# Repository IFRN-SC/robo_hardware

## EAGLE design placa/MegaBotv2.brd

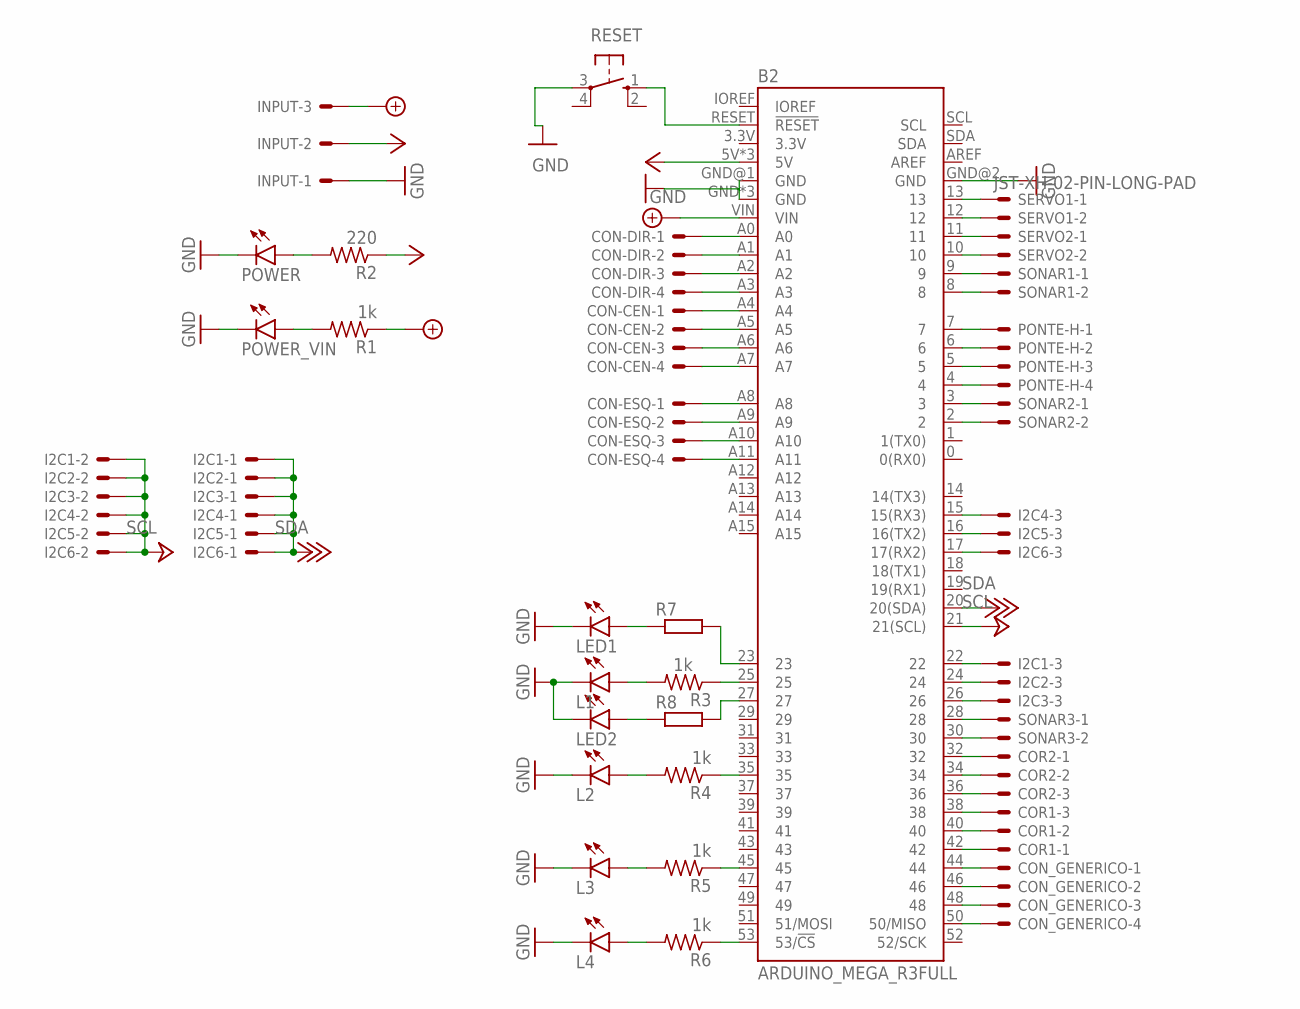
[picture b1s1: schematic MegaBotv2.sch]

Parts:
B2: ARDUINO_MEGA_R3FULL; ARDUINO_MEGA_NO_SILK
CON-CEN: JST-XH-04-PIN-LONG-PAD; JST-XH-04-PACKAGE-LONG-PAD
CON-DIR: JST-XH-04-PIN-LONG-PAD; JST-XH-04-PACKAGE-LONG-PAD
CON-ESQ: JST-XH-04-PIN-LONG-PAD; JST-XH-04-PACKAGE-LONG-PAD
CON_GENERICO: JST-XH-04-PIN-LONG-PAD; JST-XH-04-PACKAGE-LONG-PAD
COR1, COR2: JST-XH-03-PIN-LONG-PAD; JST-XH-03-PACKAGE-LONG-PAD
I2C1, I2C2, I2C3, I2C4, I2C5, I2C6: JST-XH-03-PIN-LONG-PAD; JST-XH-03-PACKAGE-LONG-PAD
INPUT: KK-156-3
L1, L2, L3, L4: LEDLED5MM_LONG_PAD; LED5MM_LONG_PAD
LED1, LED2: LEDKA-3528ASYC; KA-3528ASYC
PONTE-H: JST-XH-04-PIN-LONG-PAD; JST-XH-04-PACKAGE-LONG-PAD
POWER: LEDLED5MM_LONG_PAD; LED5MM_LONG_PAD
POWER_VIN: LEDLED5MM_LONG_PAD; LED5MM_LONG_PAD
R1, R3, R4, R5, R6: 1k; 0204/7
R2: 220; 0204/7
R7, R8: R-EU_M0805; M0805
RESET: 10-XX; B3F-10XX
SERVO1, SERVO2: JST-XH-02-PIN-LONG-PAD; JST-XH-02-PACKAGE-LONG-PAD
SONAR1, SONAR2, SONAR3: JST-XH-02-PIN-LONG-PAD; JST-XH-02-PACKAGE-LONG-PAD

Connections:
+8V: B2.VIN, INPUT.3, R1.1
+18V: B2.20 (20(SDA)), I2C1.1, I2C2.1, I2C3.1, I2C4.1, I2C5.1, I2C6.1
+24V: B2.21 (21(SCL)), I2C1.2, I2C2.2, I2C3.2, I2C4.2, I2C5.2, I2C6.2
GND: B2.GND, B2.GND@1 (GND), B2.GND@2 (GND), B2.GND@3 (GND), B2.GND@4 (GND), INPUT.1, L1.K (C), L2.K (C), L3.K (C), L4.K (C), LED1.C, LED2.C, POWER.K (C), POWER_VIN.K (C), RESET.3
unnamed: B2.7, PONTE-H.1
unnamed: B2.6, PONTE-H.2
unnamed: B2.5, PONTE-H.3
unnamed: B2.4, PONTE-H.4
unnamed: B2.A1, CON-DIR.2
unnamed: B2.A2, CON-DIR.3
unnamed: B2.A3, CON-DIR.4
unnamed: B2.A4, CON-CEN.1
unnamed: B2.A5, CON-CEN.2
unnamed: B2.A6, CON-CEN.3
unnamed: B2.A0, CON-DIR.1
unnamed: B2.A7, CON-CEN.4
unnamed: B2.A8, CON-ESQ.1
unnamed: B2.A9, CON-ESQ.2
unnamed: B2.A10, CON-ESQ.3
unnamed: B2.A11, CON-ESQ.4
unnamed: B2.11, SERVO2.1
unnamed: B2.10, SERVO2.2
unnamed: B2.9, SONAR1.1
unnamed: B2.8, SONAR1.2
unnamed: B2.22, I2C1.3
unnamed: B2.24, I2C2.3
unnamed: B2.26, I2C3.3
unnamed: B2.15 (15(RX3)), I2C4.3
unnamed: B2.16 (16(TX2)), I2C5.3
unnamed: B2.17 (17(RX2)), I2C6.3
unnamed: B2.13, SERVO1.1
unnamed: B2.12, SERVO1.2
unnamed: POWER_VIN.A, R1.2
unnamed: B2.32, COR2.1
unnamed: B2.34, COR2.2
unnamed: POWER.A, R2.2
unnamed: B2.36, COR2.3
unnamed: B2.38, COR1.3
unnamed: B2.40, COR1.2
unnamed: B2.42, COR1.1
unnamed: L1.A, R3.2
unnamed: L2.A, R4.2
unnamed: L3.A, R5.2
unnamed: L4.A, R6.2
unnamed: B2.25, R3.1
unnamed: B2.35, R4.1
unnamed: B2.45, R5.1
unnamed: B2.53 (53/!CS), R6.1
unnamed: B2.RESET (!RESET), RESET.1 (S)
unnamed: B2.3, SONAR2.1
unnamed: B2.2, SONAR2.2
unnamed: B2.28, SONAR3.1
unnamed: B2.30, SONAR3.2
unnamed: B2.44, CON_GENERICO.1
unnamed: B2.46, CON_GENERICO.2
unnamed: B2.48, CON_GENERICO.3
unnamed: B2.50 (50/MISO), CON_GENERICO.4
unnamed: LED1.A, R7.1
unnamed: B2.23, R7.2
unnamed: B2.27, R8.2
unnamed: LED2.A, R8.1
VCC: B2.5V, B2.5V@1 (5V), B2.5V@2 (5V), INPUT.2, R2.1

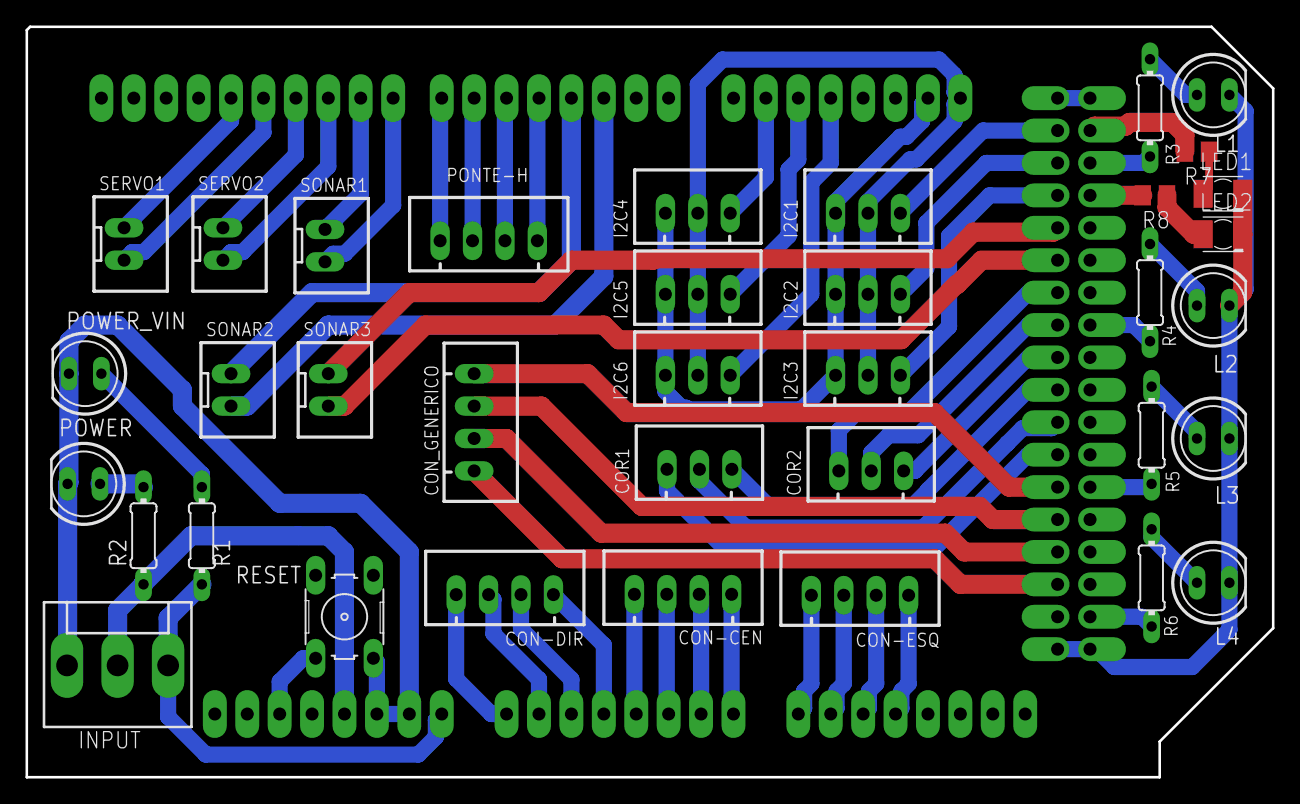
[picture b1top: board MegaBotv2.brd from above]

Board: 2 copper layers, 97.7 x 58.8 mm, 37 parts (0 on the bottom side), 62 nets.

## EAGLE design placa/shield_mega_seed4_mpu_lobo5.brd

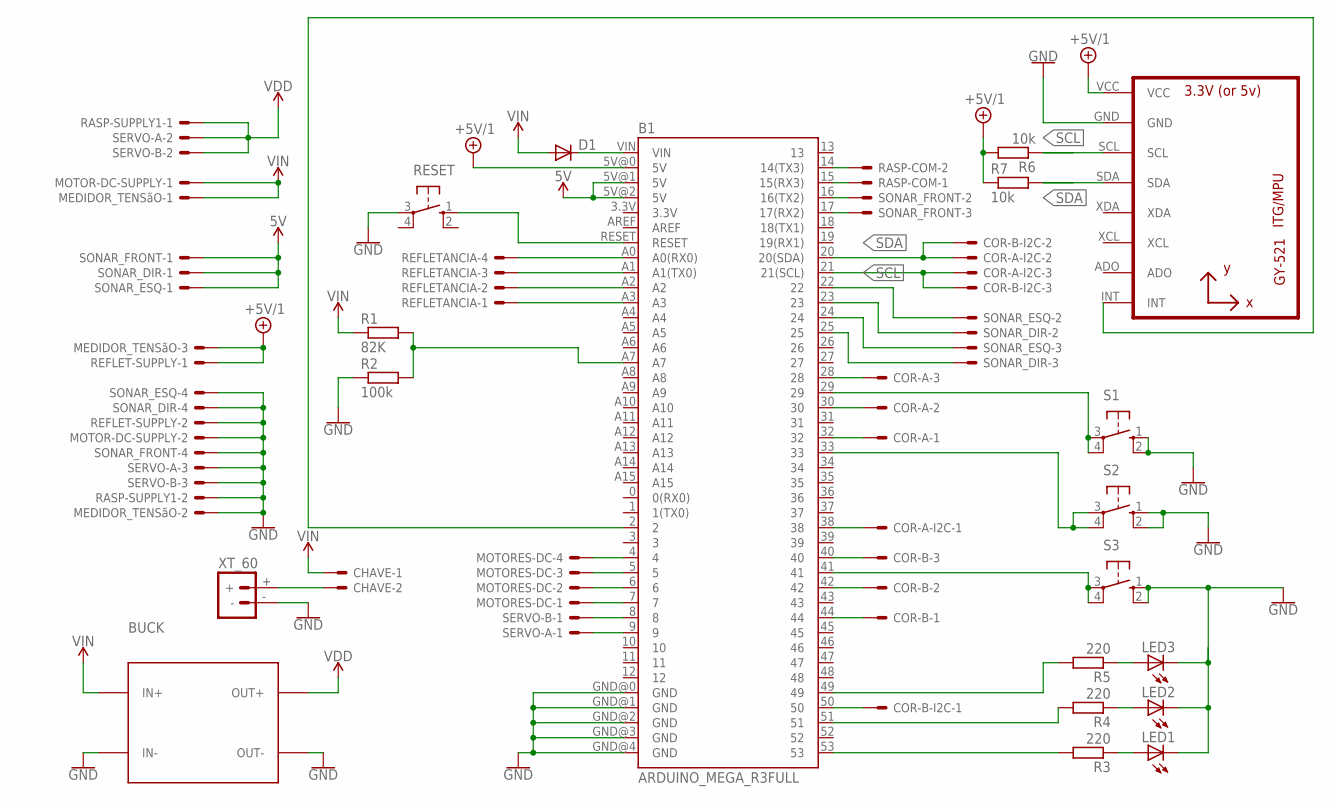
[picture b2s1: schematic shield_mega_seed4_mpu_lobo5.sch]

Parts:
B1: ARDUINO_MEGA_R3FULL; ARDUINO_MEGA
BUCK: DC-DC-STEP-DOWN-LM2596
CHAVE: 22-23-2021
COR-A: 22-23-2031
COR-A-I2C: 22-23-2031
COR-B: 22-23-2031
COR-B-I2C: 22-23-2031
D1: 1N4004; DO41-10
LED1, LED2, LED3: LED5MM
MEDIDOR_TENSãO: 22-23-2031
MOTOR-DC-SUPPLY: 22-23-2021
MOTORES-DC: 22-23-2041
R1: 82K; 0207/12
R2: 100k; 0207/12
R3, R4, R5: 220; 0207/7
R6, R7: 10k; 0204/7
RASP-COM: 22-23-2021
RASP-SUPPLY1: 22-23-2021
REFLET-SUPPLY: 22-23-2021
REFLETANCIA: 22-23-2041
RESET: 10-XX; B3F-10XX
S1, S2, S3: 10-XX; B3F-10XX
SERVO-A: 22-23-2031
SERVO-B: 22-23-2031
SONAR_DIR: 22-23-2041
SONAR_ESQ: 22-23-2041
SONAR_FRONT: 22-23-2041
U1: GY-521MPU6050; GY-521
XT_60: BATTERY_CONNXT60; XT60

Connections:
5V: B1.5V@1 (5V), B1.5V@2 (5V), SONAR_DIR.1, SONAR_ESQ.1, SONAR_FRONT.1
+5V/1: B1.5V@0 (5V), MEDIDOR_TENSãO.3, R6.2, R7.1, REFLET-SUPPLY.1, U1.VCC
GND: B1.GND@0 (GND), B1.GND@1 (GND), B1.GND@2 (GND), B1.GND@3 (GND), B1.GND@4 (GND), BUCK.IN-, BUCK.OUT-, LED1.K (C), LED2.K (C), LED3.K (C), MEDIDOR_TENSãO.2, MOTOR-DC-SUPPLY.2, R2.1, RASP-SUPPLY1.2, REFLET-SUPPLY.2, RESET.3, S1.1 (S), S1.2 (S1), S2.1 (S), S2.2 (S1), S3.1 (S), S3.2 (S1), SERVO-A.3, SERVO-B.3, SONAR_DIR.4, SONAR_ESQ.4, SONAR_FRONT.4, U1.GND, XT_60.-
unnamed: B1.A2, REFLETANCIA.2
unnamed: B1.A3, REFLETANCIA.1
unnamed: B1.4, MOTORES-DC.4
unnamed: B1.5, MOTORES-DC.3
unnamed: B1.6, MOTORES-DC.2
unnamed: B1.7, MOTORES-DC.1
unnamed: B1.8, SERVO-B.1
unnamed: B1.9, SERVO-A.1
unnamed: B1.14 (14(TX3)), RASP-COM.2
unnamed: B1.15 (15(RX3)), RASP-COM.1
unnamed: B1.16 (16(TX2)), SONAR_FRONT.2
unnamed: B1.17 (17(RX2)), SONAR_FRONT.3
unnamed: CHAVE.2, XT_60.+
unnamed: B1.32, COR-A.1
unnamed: B1.30, COR-A.2
unnamed: B1.38, COR-A-I2C.1
unnamed: B1.40, COR-B.3
unnamed: B1.42, COR-B.2
unnamed: B1.44, COR-B.1
unnamed: B1.A7, R1.2, R2.2
unnamed: B1.53, R3.2
unnamed: B1.51, R4.2
unnamed: B1.49, R5.2
unnamed: LED3.A, R5.1
unnamed: LED2.A, R4.1
unnamed: LED1.A, R3.1
unnamed: B1.33, S2.3, S2.4 (P1)
unnamed: B1.29, S1.3, S1.4 (P1)
unnamed: B1.A1 (A1(TX0)), REFLETANCIA.3
unnamed: B1.41, S3.3, S3.4 (P1)
unnamed: B1.RESET, RESET.1 (S)
unnamed: B1.VIN, D1.C
unnamed: B1.A0 (A0(RX0)), REFLETANCIA.4
unnamed: B1.25, SONAR_DIR.3
unnamed: B1.24, SONAR_ESQ.3
unnamed: B1.23, SONAR_DIR.2
unnamed: B1.22, SONAR_ESQ.2
unnamed: B1.2, U1.INT
unnamed: B1.50, COR-B-I2C.1
unnamed: B1.28, COR-A.3
SCL: B1.21 (21(SCL)), COR-A-I2C.3, COR-B-I2C.3, R6.1, U1.SCL
SDA: B1.20 (20(SDA)), COR-A-I2C.2, COR-B-I2C.2, R7.2, U1.SDA
VDD: BUCK.OUT+, RASP-SUPPLY1.1, SERVO-A.2, SERVO-B.2
VIN: BUCK.IN+, CHAVE.1, D1.A, MEDIDOR_TENSãO.1, MOTOR-DC-SUPPLY.1, R1.1

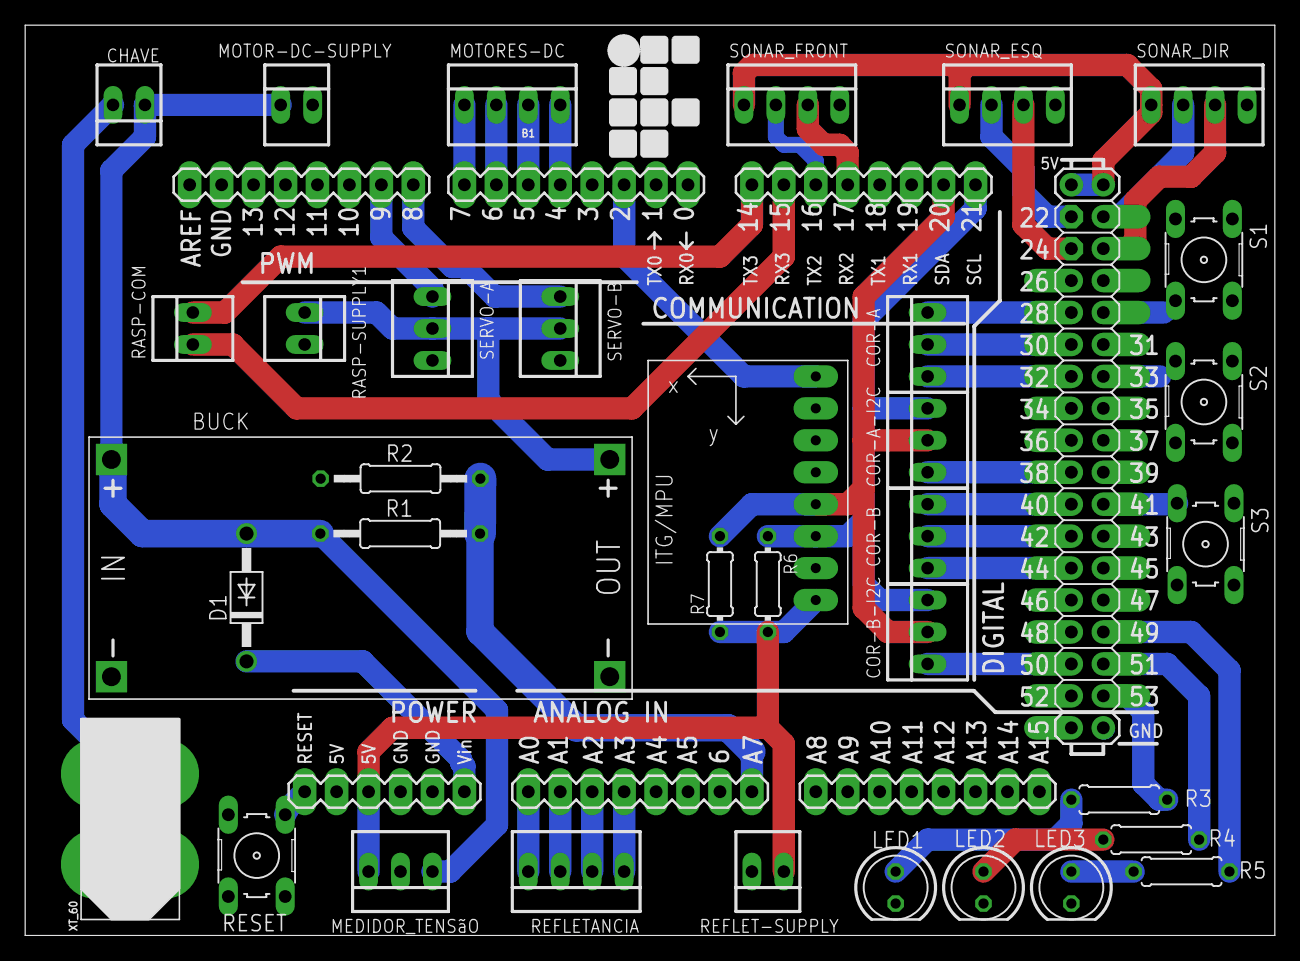
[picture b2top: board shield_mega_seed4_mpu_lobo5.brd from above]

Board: 2 copper layers, 99.4 x 72.4 mm, 36 parts (0 on the bottom side), 47 nets.

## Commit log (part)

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2017-07-06 Criada a biblioteca robo_hardware
2017-07-11 Modificado o codigo para que o sensor de linha retorne valores maiores para o branco valores menores para o preto
2017-07-11 Mudanca de nome do exemplo LerSensor.ino para LerSensorRefletancia.ino
2017-07-11 removido bug: em troca de atribuicao de valores nas variaveis valor_sensor_esq e valor_sensor_dir
2017-07-11 Modificados os pinos dos sensores de cor. Os valores anteriores dos pinos estavam gerando incompatibilidade com os pinos analógicos do arduino UNO.
2017-07-11 bug removido: erro de digitação na função de robo_hadware lerSensorLinhaEsq. Esse erro provocava um sinal negativo na função.
2017-07-11 Simplificação do progrma de acionamento dos motores, além da colocação de alguns comentários
2017-07-12 Adicionado o exemplo SonarDistancia para servir de exemplo para o que for feito com o sonsar. O erro de medição aparenta estar maior do que o esperado. Verificar!
2017-07-18 Mudança nos código de pinagem levam a alterações nos comentários existentes nos exemplos. O que foi alterado foram os exemplos que usam as funcionalidades de acionar motor e ler o sonar.
2017-07-21 Adicionadas linhas de código que permitem calibrar os sonares quando o robô é configurado. Também foi adicionada um define no .h chamado CALIBRACAO_SONAR, quanto maior o valor desse define menor será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
2017-07-21 Remoção de linhas comentadas que não eram mais utilizadas
2017-07-25 Criação de dois exemplos para ler os valores dos sensor de cor. Seja no formato HSV, seja no formato RGB.
2017-08-08 Criação de exemplos de uso: como escrever dados de calibração na EEPROM e como ler dados de calibração na EEPROM.
2017-08-09 Modificação dos nomes dos arquivos robo_hardware .cpp e .h para robo_hardware2 .cpp e .h
2017-08-18 remoção de bug relacionado ao endereço BOTAO
2017-08-21 Adicionado exemplo para testes do controle PID
2017-08-21 Declaração de pinos do arduino que serão utilizados pelo encoder.
2017-08-21 Modificação para não confundir com os pinos do arduino mega
2017-08-21 adcionada a classe contr_motor. Junto a essa classe foram adicionados dois objetos do mesmo tipo.
2017-08-21 Adicionadas os arquivos para fazer controle PID
2017-08-22 acrescentado trecho de código onde o valor do setpoint para o controle de velocidade do motor esquerdo e direito são definidos
2017-08-23 Acrescentado o valor dos motores na struct DadosLog. Criada a função printDados para mandar pela serial informações conforme o gnuplot utiliza para imprimir, a função ainda não finalizada.
2017-08-26 Modificação nome das variáveis motorEsq e motorDir para contrVeloEsq e contrVeloDir em trechos de código que ainda não haviam sido modificados antes. Modificação do mesmo trecho de código em decorrên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
2017-08-26 Modificada a constante NUM_MAX_PULSOS_POR_ROTACAO para o valor de 341.2 Acrescentada a configuração dos pinos de interrupção e direção do encoder. Ambos os pinos foram configurados como entrada (INPU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
2017-08-26 Criado exemplo para testar o controle de posicao.
2017-08-27 Mudança da constante NUM_MAX_PULSOS_POR_ROTACAO.
2017-08-27 Criação do construtor por cópia da classe encoder.
2017-08-27 Adição da classe motor ao robo_hardware. Criação de objeto motorEsq.
2017-08-27 Criação da função calculaPulso para uso do encoder. Uso da variável encoder_habilitado para só fazer uso do encoder se o mesmo tenha sido inicializado no construtor.
2017-08-27 Remoção de variáveis não mais utilizadas
2017-08-27 Utilização do macro ATOMIC_BLOCK para que as variáveis modificadas em interrupções só possam ser modificadas por uma única thread. Em outras palavras a interrupção é desabilitada dentro desse macro.
    Remoção da função CalculaAnguloRelativo e getAnguloRelativo devido a inúmeros problemas que ocorreram no uso dessa função.
    Mudança de nome de variável para ficar de acordo com o padrão. Inicialização da mesma variável de forma explicita nos construtores.
2017-08-27 Criação de função estática para o loop de controle. Essa função será chamada cada vez que ocorrer uma interrupção do timer2 o qual será configurado de acordo com o tempo amostragem do controlador dos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
2017-08-27 Acrescentado a classe MSTimer2 para utilizar a interrupção do timer2 para chamar o laço de controle.
2017-08-27 inicialização do tempo de amostragem do loop de controle de acordo com o valor tempo de amostragem armazenado na classe motor_contr.
2017-08-28 Colocando o controle de posicao dentro do laço de controle. Transformada a variavel ENCODER_HABILITADO em uma constante pois a mesma só é alterada no construtor. Criada as funções para habilitar e de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
2017-08-28 Foi acrescentada variáveis compartilhadas na classe encoder. Removido o uso do macro ATOMIC_BLOCK de dentro da classe encoder.
2017-08-28 criada função do loop de controle. Sendo chamada dentro da função as respectivas funções de controle de cada motor.
2017-08-28 Adicionada a função para escrever, na porta serial, os dados que estão gravados na EEPROM do arduino. Removido da classe robo_hardware2 e colocado na classe Log as funções que permitem gravar dados n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
2017-08-28 remoção do separador no momento de imprimir os dados pela porta serial
2017-08-28 Criação de exemplo que segue linha e grava dados na memória eeprom do arduino. Os dados gravados são valores dos sensores de refletância, valores aplicados nos motores e o tempo que foi realizada a l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
2017-08-28 colocação de linha que faltava para imprimir dados
2017-11-17 Adição da classe SD para permitir gravar em um cartão de memória SD. Implementação da função write para gravar dados no cartão de memória.
2017-11-17 colocado um retorno na função configurar da classe log. Esse retorno é para indicar que a classe log foi iniciada corretamente.
    Foi criado na struct DadosLog a função salvar tempo que se encarrega de criar uma função iniciar as variáveis "microsegundos" e "segundos". Ambas a variáveis foram transformadas em privadas.
2017-11-17 Modificado o exemplo seguirLinhaLog para se adaptar as mudanças realizadas na classe Log.
2018-04-12 Criação da Classe CorHardware que conterá a abstração para todos os hardwares para detecção de cor. Modificação do local onde as estruturas RGB e HSV estão declaradas. Tranferido do arquivo Cor.h par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
2018-04-12 Modificação da classe CorHardware com funções virtuais e com funções que devem ser immplementadas dentro da própria classe.
2018-04-12 Implementação inicial da capacidade de ligar e desligar os sensores de cor específicos dessa classe.
2018-04-12 Criado a função config para configurar as portas do arduino.
2018-04-12 Tornou a classe virtual pura
2018-04-12 Criada a classe SensoresCor
2018-04-13 Instanciados os objetos da classe CorTcs23
2018-04-14 Mudanção dos sensores para ficarem na mesma linha.
2018-04-14 Modificação do cálculo do sensor de linha para diminuir a cópia de código.
2018-04-14 Modificação do exemplo para utilizar as novas funções criadas
2018-04-14 Adição das últimas funções criadas no arquivo keywords.txt
2018-04-15 Acrescentado os sensores sonares direito e esquerdo. Deletado o sensor sonar lateral.
2018-04-15 Modificação dos comentários para ter os pinos dos arduinos uno e mega
2018-04-15 Criação da funcionalidade do botão.
2018-04-16 modificação dos arquivos botao.h e led.h para a pasta led_botoes
2018-04-16 Adição das funções de leitura dos botões ao robo_hardware
2018-04-16 Modificação para permitir que os leds pisquem duas vezes
2018-04-22 Criação de Enum e variável para diferenciar os dois tipos de sensores de cor: TCS34 e TCS23. Criada função para habilitar o funcionamento de cada tipo de sensor de cor. Comentado o trecho de código p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
2018-04-22 Adição da leitura dos sensores de cor TCS34725
2018-04-24 Declaração, e criação de funções para o sonar lateral direito
2018-04-24 alteração das portas dos sensores
2018-04-25 Mudança de pinagem dos sensores de refletância.
2018-04-30 Adicionados arquivos para o funcionamento do sensor
2018-05-06 remoção de bug relacionado ao endereço BOTAO (reverted from commit e8fe684fa55554fce2d019ace361826cfb9ed8f3)
2018-05-07 Correção dos pinos - LerSensorDistancia.ino
2018-05-16 Staged - Ignore
2018-05-24 Mudança na pinagem dos sensores de refletância
2018-06-12 Pinagem correta
2018-06-15 Pinagem dos motores e rrefletância mudada.
2018-07-03 Adição de arquivos com nomes novos para diferenciar da biblioteca original. Foi feita a modificação no MPU6050 e no MPU6050Axis_MotionApps20_hardware.
2018-07-03 Remoção de bug
    Declaração da variável estática mpuInterrupt dentro do .cpp para permitir do a compilação do código.
2018-07-07 Separação de funcionalidades
    Criação de 3 funções diferentes para facilitar a análise do que pode ser feito para fazer o mpu6050 funcionar da forma que se deseja.
2018-07-07 Remoção de bug que travava comunicação
    -Foi removido "whiles" do código que travavam o código quando era realizada checagem se os dados estavam ok. Os whiles foram removidos por if.
    -Também foi implementado o retorno dos dados: yaw, pitch e roll.
    -Foi colocado o retorno de uma struct.
2018-07-07 Remoção de função
    Remoção de função anteriormente utilizada para imprimir dados pela porta serial.
2018-07-08 Adicionada função
    Adicionada função para realizar a leitura do sensor IMU.
2018-07-08 mudada a pinagem ds sensores de cor analógico
    Mudado os pinos dos sensores que não se comunicam por i2c para se adequar a placa shield atual.
2018-07-08 Modificado nome de pino
    Modificado o nome do pino da interrupção da IMU para se enquadrar no padrão já utilizado.
2018-08-08 Struct "calibracao_dados" mudada para padrão e adicionados valores HSV para sensores de cor. Também foram alterados os exemplos referentes a memória EEPROM.
2018-08-24 ALteração na pinagem:
    -refletância;
    -cor analógico;
2018-08-24 Alteração na pinagem:
    Alteração do sensor de refletância e do sonar para placa de sensores nova.
2018-08-28 Criação do branch para utilização do motor de passo
2018-09-05 Correção de bug.
2018-09-14 Biblioteca atualizada para a nova versa_mega
2018-09-19 Pinos alterados para consertar o problema do sentido do motor.
2018-09-20 Variável que armazena o tipo do sensor de cor atualizada para static.
2018-09-26 Remoção de arquivo
    Remoção do arquivo Conversao.h
2018-09-27 Incluído o sensor encoder no robo_hardware
2018-09-27 Criado novo exemplo
    Criado novo exemplo que utiliza o encoder para determinar em que posição o motor deve ficar.
2018-09-28 Criação da classe Time
    Criação dessa classe para lidar com o tempo necessário para realizar o cálculo da velocidade.
2018-09-28 Radianos para graus e graus para radianos
    Criadas funções que transformam graus para radianos e radianos para graus
2018-09-28 remoção de bug na leitura da velocidade
    Falta converter a velocidade para graus por segundo
2018-09-28 Criação de exemplo
    Criação de exemplo para testar o controle PID do robô
2018-10-22 Novas funções
    Foram criadas novas funções para os sensores de fim de curso.
2018-10-24 Espacos sem necessidade
2018-10-25 Precisei mudar a pinagem das rodas mais uma vez.
2018-11-12 Exemplos de uso do sensor de cor atualizados.
2019-02-12 Mudanças para testes da nova estratégia para leitura dos sensores.
2019-02-14 Delay depois de ligar/desligar o led adicionado
2019-02-22 ajuste na pinagem e na função de leitura individual
2019-02-27 Adição de novas funções
    Para manter padronizada a leitura dos sensores de refletancia.
2019-02-27 Resolução de bug.
    Alteração da primeira case de sensor DIREITO para ESQUERDO.
2019-03-20 Métodos de acionarGarra atualizados.
2019-03-25 Pino do servo motor que estava trocado consertado
2019-03-26 Pinagem do sonar alterada
2019-04-11 Adição do refletancia 100 interferência para o sensor do MEIO (5sensor).
2019-04-13 Alteração na pinagem: sensores de refletancia entre A1 e A3, ambos estavam invertidos
2019-05-02 adicionei a pinagem do sensor no switch
2019-05-02 Revert "criei funções para ler o valor do sensor na garra"
    This reverts commit c75928e0291128bf3b1937fbda05e1e72e0a245a.
2019-05-02 adicionei um novo sensor a biblioteca
2019-05-02 adicionei um novo sensor na biblioteca
2019-05-16 Tempo de espera do sonar alterado.
2019-06-05 Adição de pinagem para o sensor de cor
2019-06-26 correção
    foi adicionado um ponto e virgula.
2019-07-23 PINAGEN
    foi adicionado umapinagem para um novo sensor de fim de curso
2019-08-02 Adição V2
2019-09-18 Adicionados os motores de passo
2019-09-26 Pequena alteração na pinagem dos motores
2019-10-03 - Pinagem.h : defini pinagem para dois fim de curso
2019-10-15 Adicionado exemplo de garras
2023-09-07 Tentativa de alinhar os defines da classe pinagem

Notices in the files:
parts and their libraries:
SparkFun-Boards: Licensing: Creative Commons ShareAlike 4.0 International - https://creativecommons.org/licenses/by-sa/4.0
